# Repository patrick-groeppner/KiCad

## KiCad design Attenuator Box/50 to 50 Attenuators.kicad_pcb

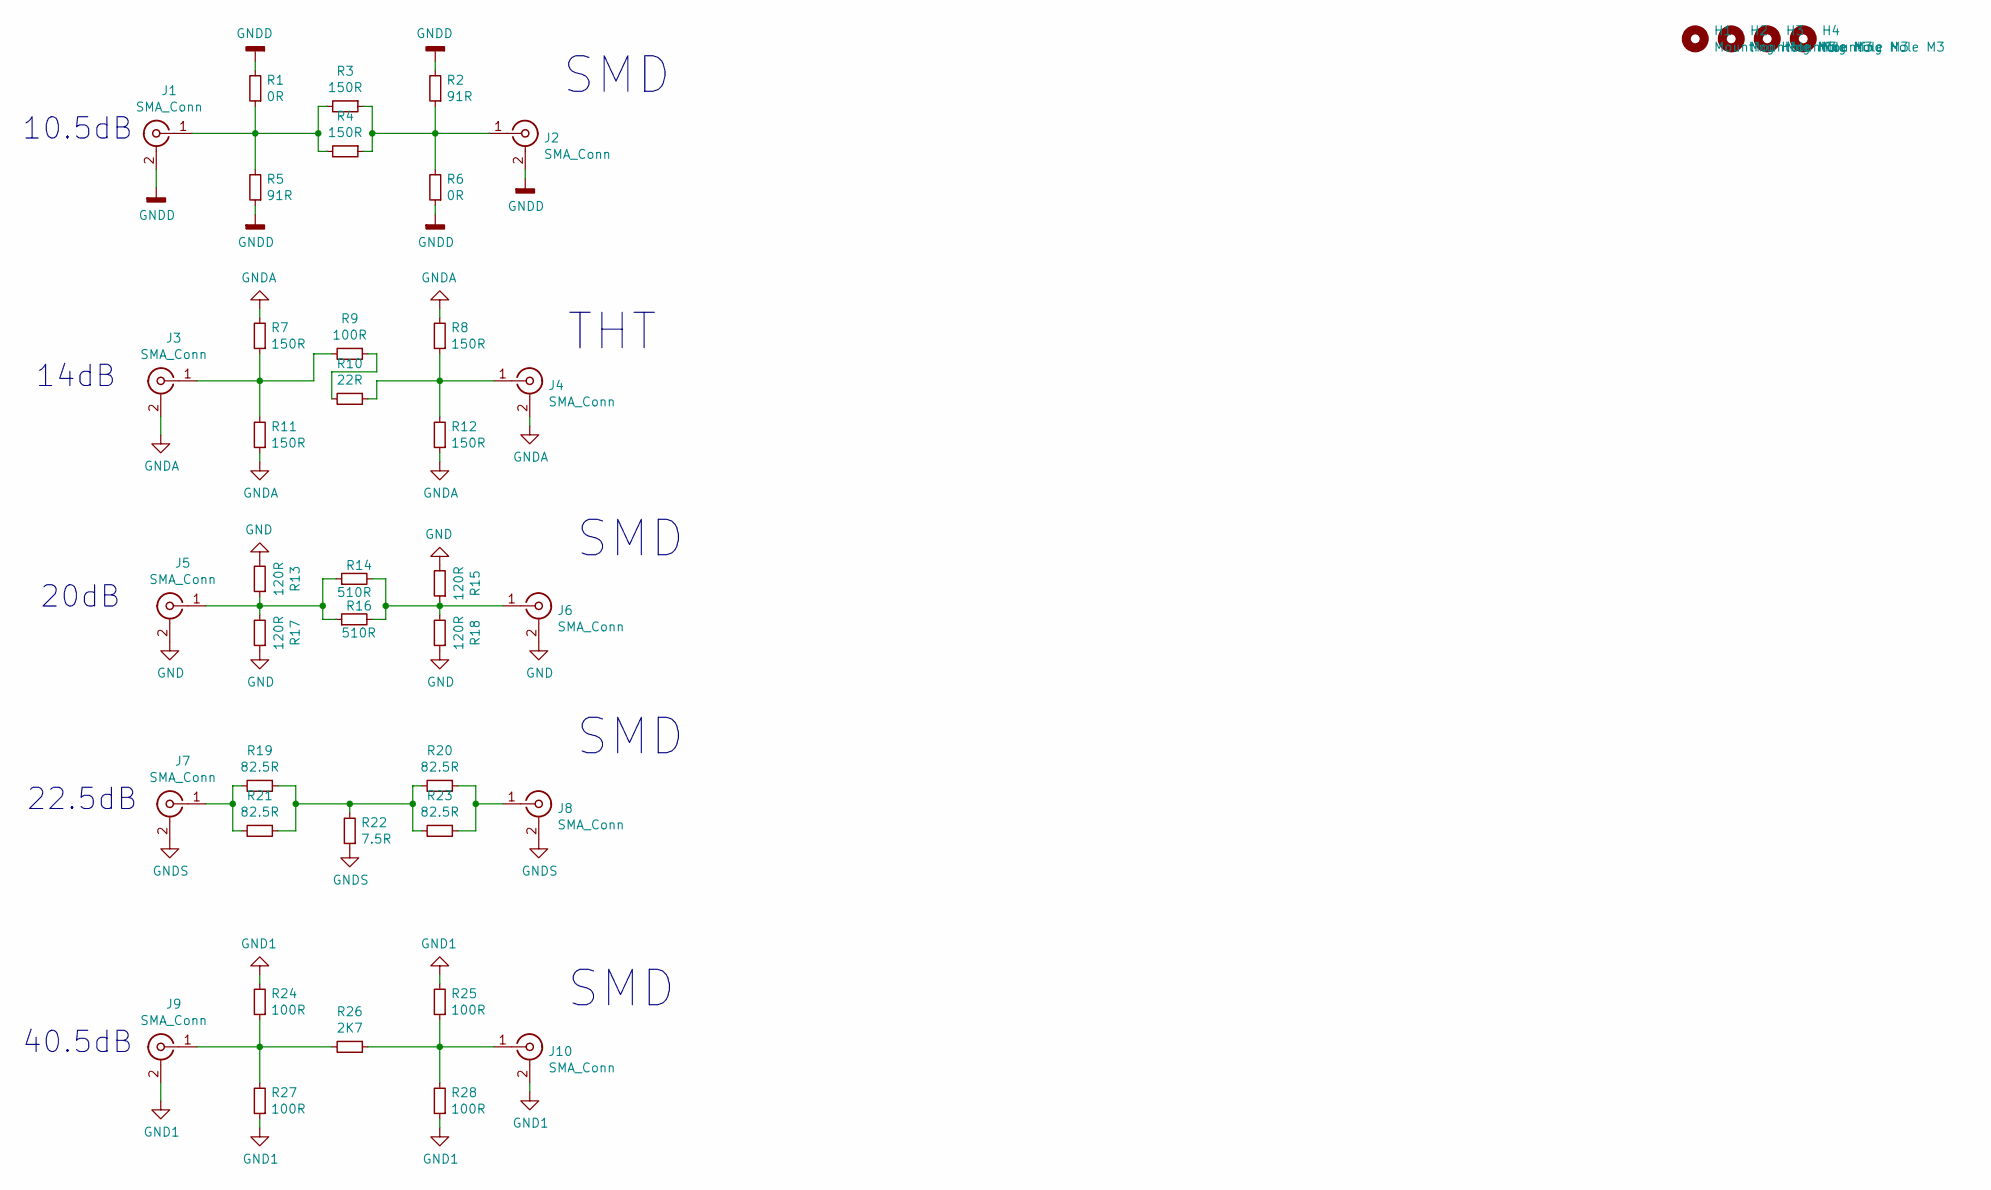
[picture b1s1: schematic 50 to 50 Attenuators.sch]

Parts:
H1, H2, H3, H4: Mounting Hole M3; MountingHole_3.2mm_M3_DIN965_Pad
J1, J2, J3, J4, J5, J6, J7, J8, J9, J10: SMA_Conn; Samtec_SMA-J-P-X-ST-EM1_EdgeMount
R1, R6: 0R; R_1206_3216Metric_Pad1.30x1.75mm_HandSolder
R2, R5: 91R; R_1206_3216Metric_Pad1.30x1.75mm_HandSolder
R3, R4: 150R; R_1206_3216Metric_Pad1.30x1.75mm_HandSolder
R7, R8, R11, R12: 150R; R_Axial_DIN0207_L6.3mm_D2.5mm_P7.62mm_Horizontal
R9: 100R; R_Axial_DIN0207_L6.3mm_D2.5mm_P7.62mm_Horizontal
R10: 22R; R_Axial_DIN0207_L6.3mm_D2.5mm_P7.62mm_Horizontal
R13, R15, R17, R18: 120R; R_1206_3216Metric_Pad1.30x1.75mm_HandSolder
R14, R16: 510R; R_1206_3216Metric_Pad1.30x1.75mm_HandSolder
R19, R20, R21, R23: 82.5R; R_1206_3216Metric_Pad1.30x1.75mm_HandSolder
R22: 7.5R; R_1206_3216Metric_Pad1.30x1.75mm_HandSolder
R24, R25, R27, R28: 100R; R_1206_3216Metric_Pad1.30x1.75mm_HandSolder
R26: 2K7; R_1206_3216Metric_Pad1.30x1.75mm_HandSolder

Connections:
GND: J5.2 (Ext), J6.2 (Ext), R13.2, R15.2, R17.1, R18.1
GND1: J9.2 (Ext), J10.2 (Ext), R24.2, R25.2, R27.1, R28.1
GNDA: J3.2 (Ext), J4.2 (Ext), R7.2, R8.2, R11.1, R12.1
GNDD: J1.2 (Ext), J2.2 (Ext), R1.2, R2.2, R5.1, R6.1
GNDS: J7.2 (Ext), J8.2 (Ext), R22.1
unnamed: J1.1 (In), R1.1, R3.2, R4.2, R5.2
unnamed: J2.1 (In), R2.1, R3.1, R4.1, R6.2
unnamed: J3.1 (In), R7.1, R9.2, R11.2
unnamed: J4.1 (In), R8.1, R10.1, R12.2
unnamed: J5.1 (In), R13.1, R14.1, R16.1, R17.2
unnamed: J6.1 (In), R14.2, R15.1, R16.2, R18.2
unnamed: J7.1 (In), R19.2, R21.2
unnamed: J8.1 (In), R20.1, R23.1
unnamed: J9.1 (In), R24.1, R26.2, R27.2
unnamed: J10.1 (In), R25.1, R26.1, R28.2
unnamed: R9.1, R10.2
unnamed: R19.1, R20.2, R21.1, R22.2, R23.2

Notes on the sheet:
THT
SMD
14dB
10.5dB
22.5dB
20dB
40.5dB

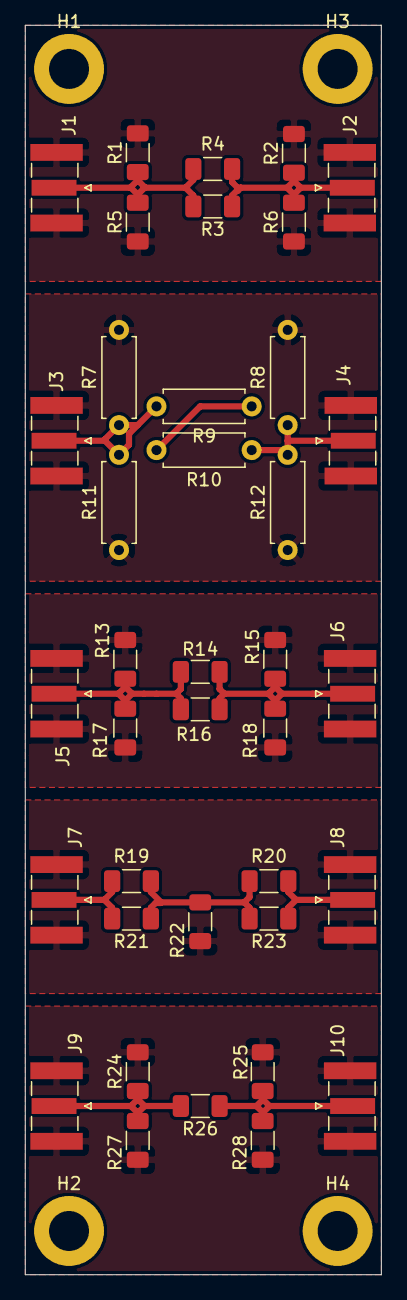
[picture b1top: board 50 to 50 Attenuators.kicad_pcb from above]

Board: 2 copper layers, 28.5 x 100.0 mm, 42 parts (0 on the bottom side), 17 nets.

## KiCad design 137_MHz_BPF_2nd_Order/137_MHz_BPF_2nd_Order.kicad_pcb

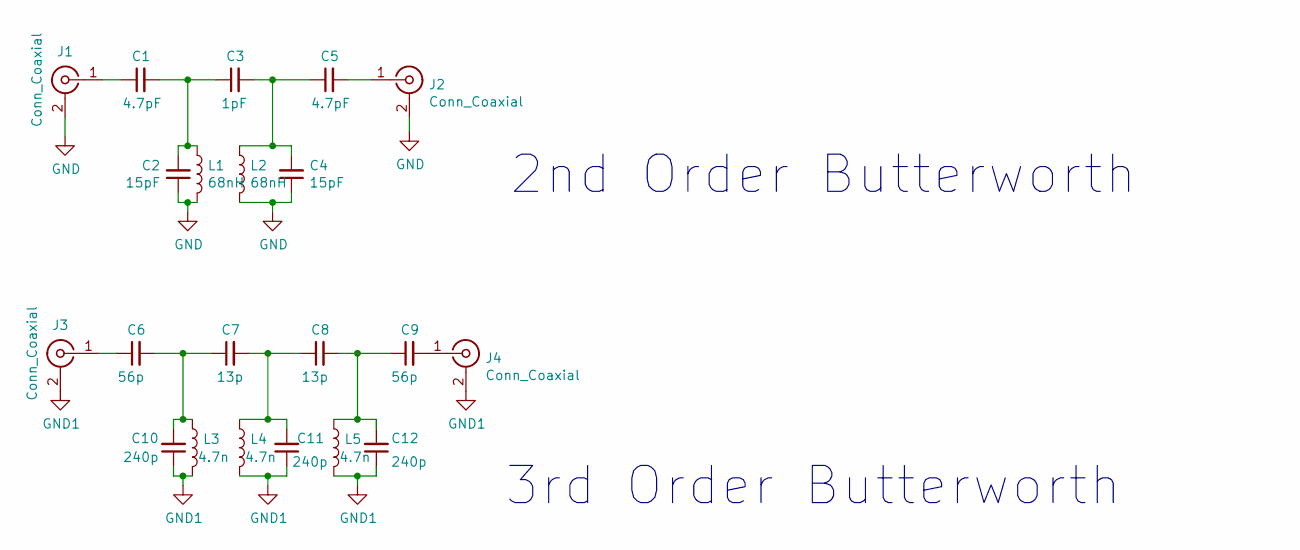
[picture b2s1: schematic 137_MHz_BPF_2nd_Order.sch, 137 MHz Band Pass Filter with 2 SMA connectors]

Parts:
C1, C5: 4.7pF; C_0603_1608Metric_Pad1.08x0.95mm_HandSolder
C2, C4: 15pF; C_0603_1608Metric_Pad1.08x0.95mm_HandSolder
C3: 1pF; C_0603_1608Metric_Pad1.08x0.95mm_HandSolder
C6, C9: 56p; C_0603_1608Metric_Pad1.08x0.95mm_HandSolder
C7, C8: 13p; C_0603_1608Metric_Pad1.08x0.95mm_HandSolder
C10, C11, C12: 240p; C_0603_1608Metric_Pad1.08x0.95mm_HandSolder
J1, J2, J3, J4: Conn_Coaxial; Samtec_SMA-J-P-X-ST-EM1_EdgeMount
L1, L2: 68nH; L_0603_1608Metric_Pad1.05x0.95mm_HandSolder
L3, L4, L5: 4.7n; L_0603_1608Metric_Pad1.05x0.95mm_HandSolder

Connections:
GND: C2.1, C4.1, J1.2 (Ext), J2.2 (Ext), L1.2, L2.2
GND1: C10.1, C11.1, C12.1, J3.2 (Ext), J4.2 (Ext), L3.2, L4.2, L5.2
unnamed: C1.1, J1.1 (In)
unnamed: C1.2, C2.2, C3.1, L1.1
unnamed: C3.2, C4.2, C5.1, L2.1
unnamed: C5.2, J2.1 (In)
unnamed: C6.1, J3.1 (In)
unnamed: C9.2, J4.1 (In)
unnamed: C6.2, C7.1, C10.2, L3.1
unnamed: C7.2, C8.1, C11.2, L4.1
unnamed: C8.2, C9.1, C12.2, L5.1

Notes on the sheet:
2nd Order Butterworth
3rd Order Butterworth

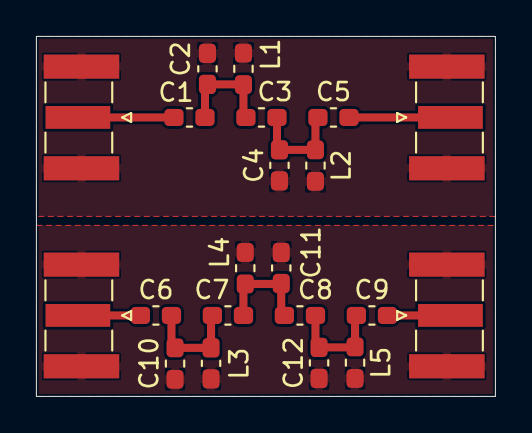
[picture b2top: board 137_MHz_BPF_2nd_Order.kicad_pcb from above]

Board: 2 copper layers, 25.5 x 20.0 mm, 21 parts (0 on the bottom side), 11 nets.

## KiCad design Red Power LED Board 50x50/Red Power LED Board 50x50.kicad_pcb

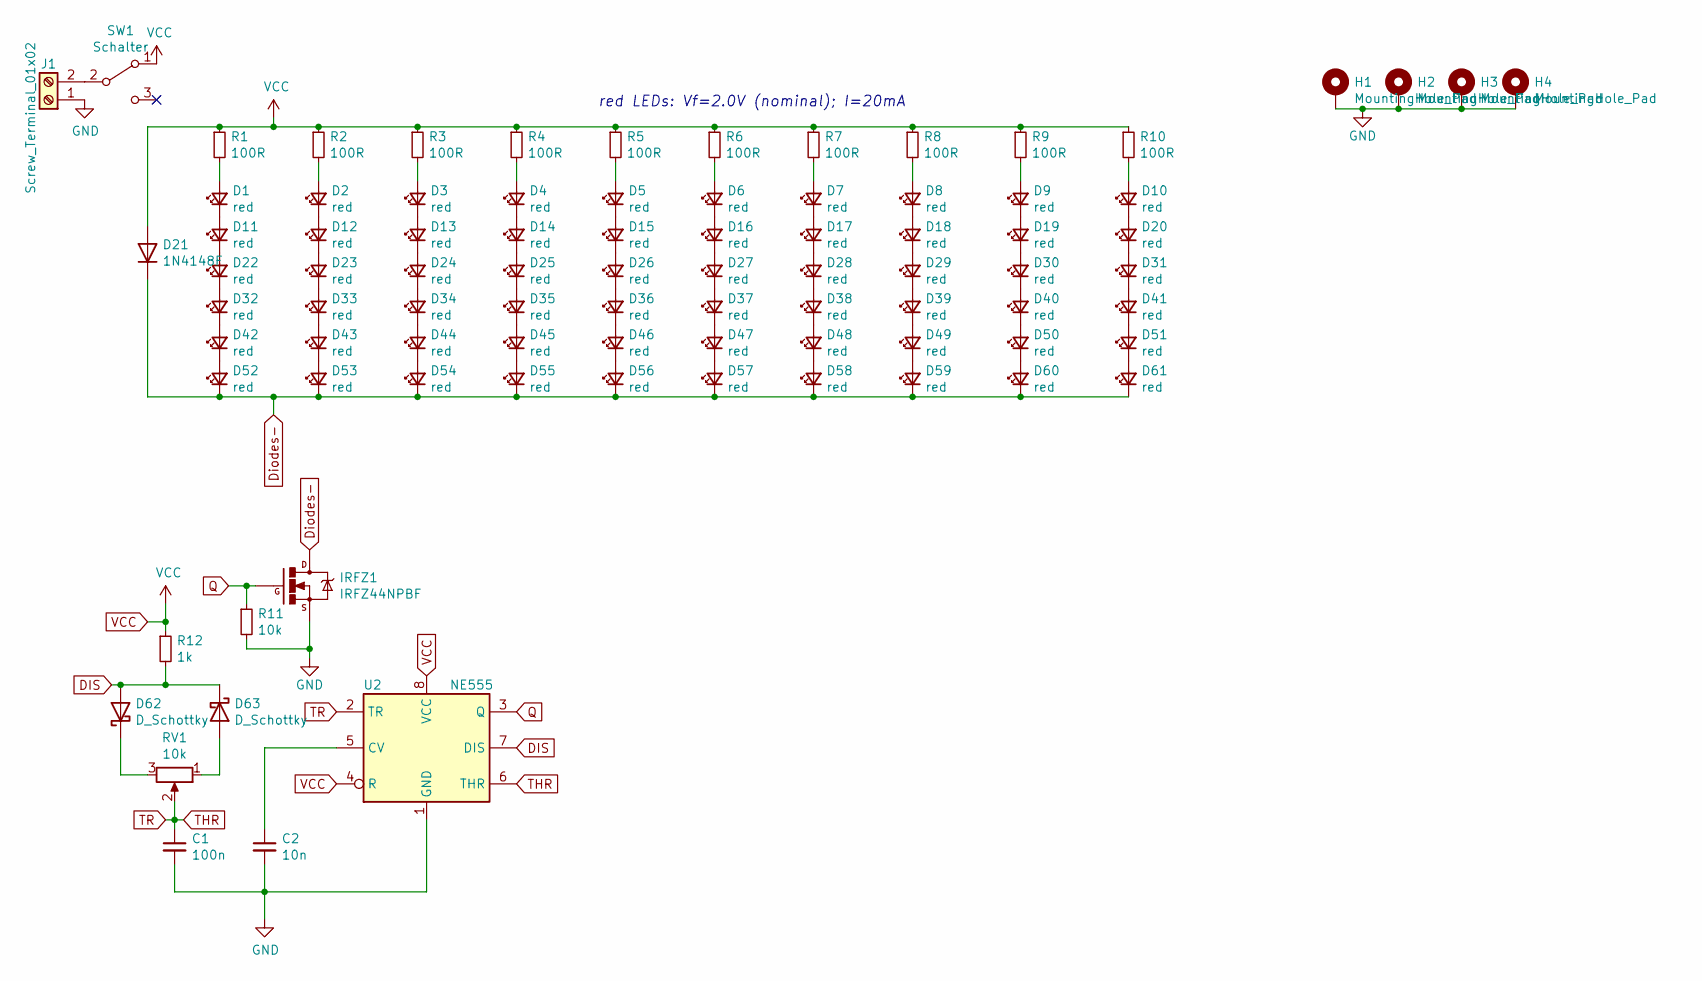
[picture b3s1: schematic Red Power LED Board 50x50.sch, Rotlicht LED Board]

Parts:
C1: 100n; C_0603_1608Metric; LCSC Part # C14663
C2: 10n; C_0603_1608Metric; LCSC Part # C57112
D1, D2, D3, D4, D5, D6, D7, D8, D9, D10, D11, D12, D13, D14, D15, D16, D17, D18, D19, D20, D22, D23, D24, D25, D26, D27, D28, D29, D30, D31, D32, D33, D34, D35, D36, D37, D38, D39, D40, D41, D42, D43, D44, D45, D46, D47, D48, D49, D50, D51, D52, D53, D54, D55, D56, D57, D58, D59, D60, D61: red; LED_0805_2012Metric; LCSC Part # C84256
D21: 1N4148F; D_SOD-123; LCSC Part # C81598
D62, D63: D_Schottky; D_0805_2012Metric; LCSC Part # C2480
H1, H2, H3, H4: MountingHole_Pad; MountingHole_3.2mm_M3_Pad_Via
IRFZ1: IRFZ44NPBF; IRFZ44N-TO-220_Horizontal_
J1: Screw_Terminal_01x02; TerminalBlock_bornier-2_P5.08mm
R1, R2, R3, R4, R5, R6, R7, R8, R9, R10: 100R; R_1206_3216Metric; LCSC Part # C17901
R11: 10k; R_0805_2012Metric; LCSC Part # C17414
R12: 1k; R_0805_2012Metric; LCSC Part # C17513
RV1: 10k; THT_Poti
SW1: Schalter; SWITCH_SPDT_PTH_11.6X4.0MM
U2: NE555; DIP-8_W7.62mm_LongPads

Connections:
DIS: D62.2 (A), D63.1 (K), R12.2, U2.7 (DIS)
Diodes-: D21.1 (K), D52.1 (K), D53.1 (K), D54.1 (K), D55.1 (K), D56.1 (K), D57.1 (K), D58.1 (K), D59.1 (K), D60.1 (K), D61.1 (K), IRFZ1.2
GND: C1.2, C2.2, H1.1, H2.1, H3.1, H4.1, IRFZ1.3, J1.1, R11.2, U2.1 (GND)
unnamed: C2.1, U2.5 (CV)
unnamed: D1.1 (K), D11.2 (A)
unnamed: D1.2 (A), R1.2
unnamed: D2.2 (A), R2.2
unnamed: D3.2 (A), R3.2
unnamed: D4.2 (A), R4.2
unnamed: D5.2 (A), R5.2
unnamed: D6.2 (A), R6.2
unnamed: D7.2 (A), R7.2
unnamed: D8.2 (A), R8.2
unnamed: D9.2 (A), R9.2
unnamed: D10.1 (K), D20.2 (A)
unnamed: D10.2 (A), R10.2
unnamed: D11.1 (K), D22.2 (A)
unnamed: D12.1 (K), D23.2 (A)
unnamed: D2.1 (K), D12.2 (A)
unnamed: D13.1 (K), D24.2 (A)
unnamed: D3.1 (K), D13.2 (A)
unnamed: D14.1 (K), D25.2 (A)
unnamed: D4.1 (K), D14.2 (A)
unnamed: D15.1 (K), D26.2 (A)
unnamed: D5.1 (K), D15.2 (A)
unnamed: D16.1 (K), D27.2 (A)
unnamed: D6.1 (K), D16.2 (A)
unnamed: D17.1 (K), D28.2 (A)
unnamed: D7.1 (K), D17.2 (A)
unnamed: D18.1 (K), D29.2 (A)
unnamed: D8.1 (K), D18.2 (A)
unnamed: D19.1 (K), D30.2 (A)
unnamed: D9.1 (K), D19.2 (A)
unnamed: D20.1 (K), D31.2 (A)
unnamed: D22.1 (K), D32.2 (A)
unnamed: D23.1 (K), D33.2 (A)
unnamed: D24.1 (K), D34.2 (A)
unnamed: D25.1 (K), D35.2 (A)
unnamed: D26.1 (K), D36.2 (A)
unnamed: D27.1 (K), D37.2 (A)
unnamed: D28.1 (K), D38.2 (A)
unnamed: D29.1 (K), D39.2 (A)
unnamed: D30.1 (K), D40.2 (A)
unnamed: D31.1 (K), D41.2 (A)
unnamed: D32.1 (K), D42.2 (A)
unnamed: D33.1 (K), D43.2 (A)
unnamed: D34.1 (K), D44.2 (A)
unnamed: D35.1 (K), D45.2 (A)
unnamed: D36.1 (K), D46.2 (A)
unnamed: D37.1 (K), D47.2 (A)
unnamed: D38.1 (K), D48.2 (A)
unnamed: D39.1 (K), D49.2 (A)
unnamed: D40.1 (K), D50.2 (A)
unnamed: D41.1 (K), D51.2 (A)
unnamed: D42.1 (K), D52.2 (A)
unnamed: D43.1 (K), D53.2 (A)
unnamed: D44.1 (K), D54.2 (A)
unnamed: D45.1 (K), D55.2 (A)
unnamed: D46.1 (K), D56.2 (A)
unnamed: D47.1 (K), D57.2 (A)
unnamed: D48.1 (K), D58.2 (A)
unnamed: D49.1 (K), D59.2 (A)
unnamed: D50.1 (K), D60.2 (A)
unnamed: D51.1 (K), D61.2 (A)
unnamed: D62.1 (K), RV1.3
unnamed: D63.2 (A), RV1.1
unnamed: J1.2, SW1.2 (B)
Q: IRFZ1.1, R11.1, U2.3 (Q)
THR: C1.1, RV1.2, U2.2 (TR), U2.6 (THR)
VCC: D21.2 (A), R1.1, R2.1, R3.1, R4.1, R5.1, R6.1, R7.1, R8.1, R9.1, R10.1, R12.1, SW1.1 (A), U2.4 (R), U2.8 (VCC)

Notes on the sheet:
red LEDs: Vf=2.0V (nominal); I=20mA

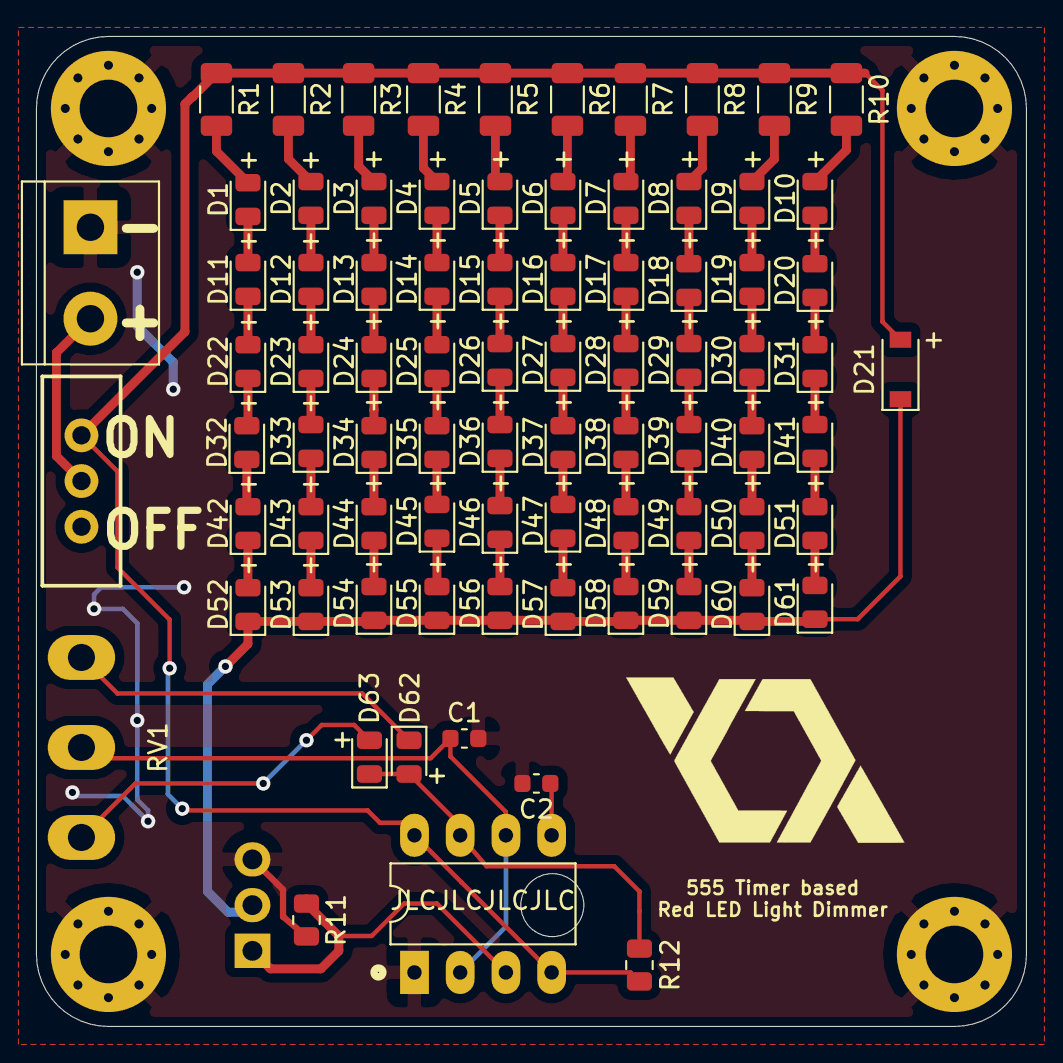
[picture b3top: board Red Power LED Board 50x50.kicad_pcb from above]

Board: 2 copper layers, 55.0 x 55.0 mm, 86 parts (1 on the bottom side), 70 nets.

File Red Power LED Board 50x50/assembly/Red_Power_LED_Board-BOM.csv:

Designator,Quantity,Value,Footprint,LCSC Part #
"C1, ",1,100n,603,C14663
"C2, ",1,10n,603,C57112
"D1, D2, D3, D4, D5, D6, D7, D8, D9, D10, D11, D12, D13, D14, D15, D16, D17, D18, D19, D20, D22, D23, D24, D25, D26, D27, D28, D29, D30, D31, D32, D33, D34, D35, D36, D37, D38, D39, D40, D41, D42, D43, D44, D45, D46, D47, D48, D49, D50, D51, D52, D53, D54, D55, D56, D57, D58, D59, D60, D61, ",60,red,805,C84256
"D21, ",1,DIODE-1N4148,SOD-123,C81598
"D62, D63, ",2,D_Schottky,805,C2480
"R1, R2, R3, R4, R5, R6, R7, R8, R9, R10, ",10,100R,1206,C17901
"R11, ",1,10k,805,C17414
"R12, ",1,1k,805,C17513

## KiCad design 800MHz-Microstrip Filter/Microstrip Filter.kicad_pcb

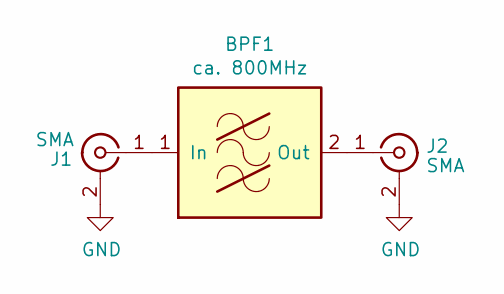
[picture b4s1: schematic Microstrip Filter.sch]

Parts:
BPF1: ca. 800MHz; Microstrip_Hairpin_BPF_800MHz
J1, J2: SMA; Samtec_SMA-J-P-X-ST-EM1_EdgeMount

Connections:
GND: J1.2 (Ext), J2.2 (Ext)
unnamed: BPF1.1 (In), J1.1 (In)
unnamed: BPF1.2 (Out), J2.1 (In)

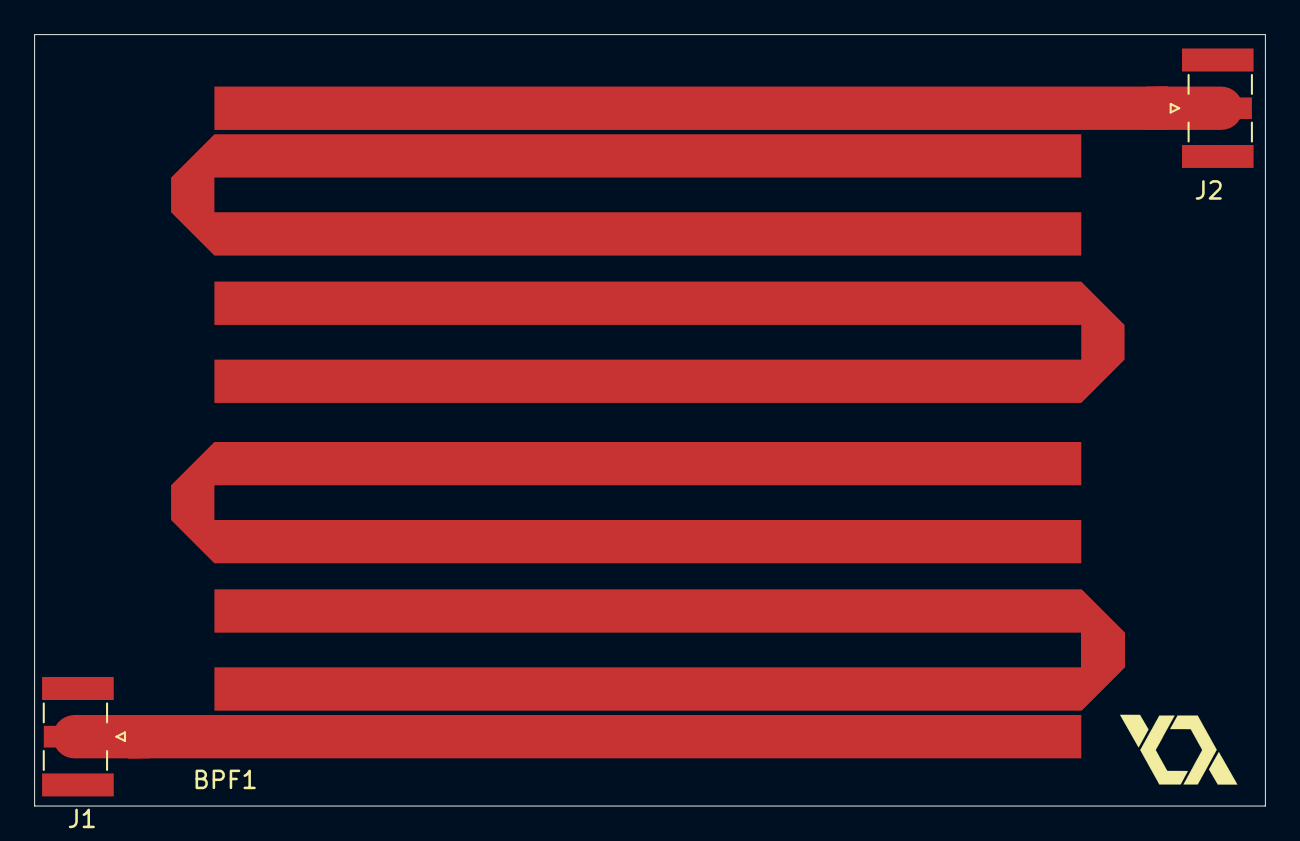
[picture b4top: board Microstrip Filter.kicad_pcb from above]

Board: 2 copper layers, 72.1 x 45.2 mm, 3 parts (0 on the bottom side), 3 nets.
